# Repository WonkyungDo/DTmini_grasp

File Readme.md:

# DenseTact Mini 

# DenseTact mini Evaluation code
## franka arm
## allegro hand
## Tactile Sensor
## pipeline code

# DenseTact Design file
fingernail stl, case stl, M1.6 screw / nuts, gel fabrication method, camera spec 
mold for gel, and mold for mold of the gel

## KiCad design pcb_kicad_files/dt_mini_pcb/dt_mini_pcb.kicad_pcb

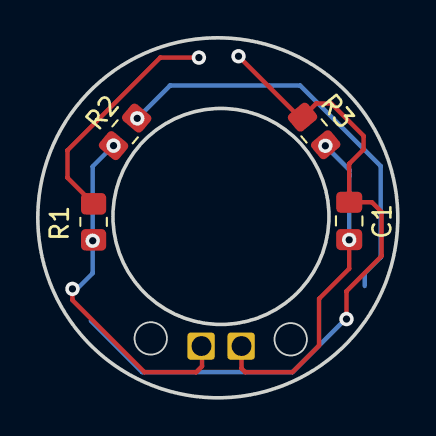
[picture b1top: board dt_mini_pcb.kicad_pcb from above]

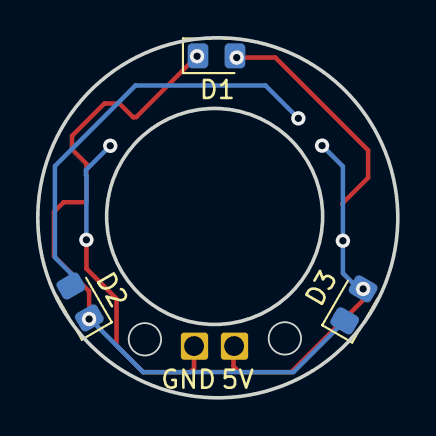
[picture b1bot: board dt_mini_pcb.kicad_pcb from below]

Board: 2 copper layers, 20.0 x 20.0 mm, 9 parts (5 on the bottom side), 5 nets.

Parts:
C1: C; C_0805_2012Metric_Pad1.18x1.45mm_HandSolder
D1: LED Green; LED_0805_2012Metric_Pad1.15x1.40mm_HandSolder
D2: LED Red; LED_0805_2012Metric_Pad1.15x1.40mm_HandSolder
D3: LED Blue; LED_0805_2012Metric_Pad1.15x1.40mm_HandSolder
R1: 34.7Ω; R_0805_2012Metric_Pad1.20x1.40mm_HandSolder
R2: 30.7Ω; R_0805_2012Metric_Pad1.20x1.40mm_HandSolder
R3: 18.8Ω; R_0805_2012Metric_Pad1.20x1.40mm_HandSolder
TP1: 5V; SolderWire-0.5sqmm_1x01_D0.9mm_OD2.1mm
TP2: GND; SolderWire-0.5sqmm_1x01_D0.9mm_OD2.1mm

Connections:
+5V: D3.2 (A), R1.1, R2.1, TP1.1
GND: C1.2, R3.2, TP2.1
unnamed: C1.1, D1.1 (K), D2.1 (K), D3.1 (K), R3.1
unnamed: D1.2 (A), R1.2
unnamed: D2.2 (A), R2.2

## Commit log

2023-09-09 pipeline with recorded jnt info (only fng done)
2023-09-09 readme
2023-09-09 adding allegro hand controller component
2023-09-10 todo: franka arm - allegro connection
2023-09-10 recording motion saved, pipelinings
2023-09-11 pipeline code update
2023-09-11 evaluation starting
2023-09-11 fix error for tap_check state
2023-09-12 Adding tactile_sensor: object detector and camera stream pipeline
2023-09-12 franka arm code update
2023-09-12 pub example
2023-09-12 adding PCB files
2023-09-15 some tests
2023-09-16 changing path
    changing path
2023-09-28 uploading design files
